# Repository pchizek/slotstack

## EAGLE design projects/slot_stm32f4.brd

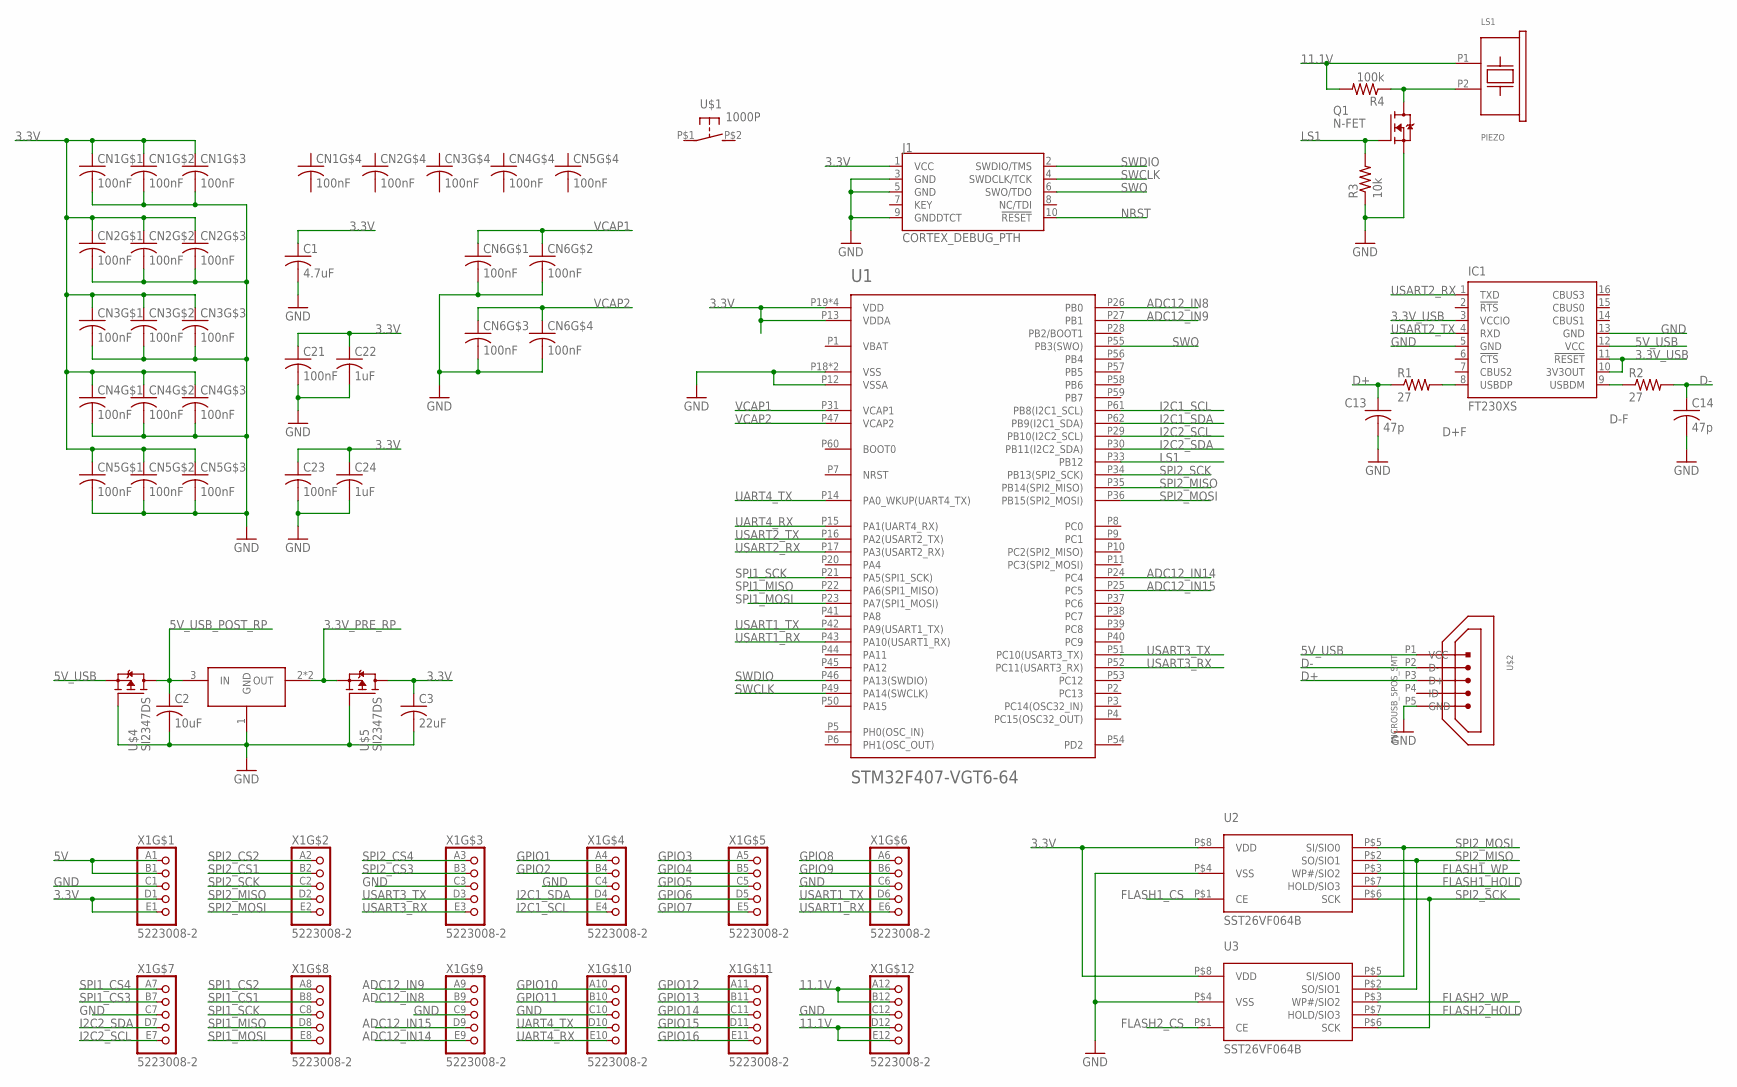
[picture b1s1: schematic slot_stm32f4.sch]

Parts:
C1: 4.7uF; C0805
C2: 10uF; C0805
C3: 22uF; C0805
C13, C14: 47p; C0603
C21, C23: 100nF; C0805
C22, C24: 1uF; C0805
CN1, CN2, CN3, CN4, CN5, CN6: 100nF; CNET_4POS_0612
IC1: FT230XS; SSOP16
J1: CORTEX_DEBUG_PTH; 2X5-PTH-1.27MM
LS1: PIEZO; PKMCS0909E400-R1
Q1: N-FET; NMINI3-R1-B
R1, R2: 27; R0603
R3: 10k; R0603
R4: 100k; R0603
U1: STM32F407-VGT6-64; LQFP64
U2, U3: SST26VF064B; SOIJ
U$1: 1000P; B3U-1000P
U$2: MICROUSB_5POS_SMT; RECPT_SMT_R/A
U$3: AZ1117C; SOT89
U$4, U$5: SI2347DS; SOT23
X1: 5223008-2

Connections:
3.3V: C1.1, C3.1, C21.1, C22.1, C23.1, C24.1, CN1.C1A (1), CN1.C2A (1), CN1.C3A (1), CN2.C1A (1), CN2.C2A (1), CN2.C3A (1), CN3.C1A (1), CN3.C2A (1), CN3.C3A (1), CN4.C1A (1), CN4.C2A (1), CN4.C3A (1), CN5.C1A (1), CN5.C2A (1), CN5.C3A (1), J1.1 (VCC), U1.P13 (VDDA), U1.P19 (VDD), U1.P32 (VDD), U1.P48 (VDD), U1.P64 (VDD), U2.P$8 (VDD), U3.P$8 (VDD), U$5.3 (D), X1.D1 (4), X1.E1 (5)
3.3V_PRE_RP: U$3.2 (OUT), U$3.2@1 (OUT), U$5.2 (S)
3.3V_USB: IC1.3 (VCCIO), IC1.10 (3V3OUT), IC1.11 (!RESET)
5V: X1.A1 (1), X1.B1 (2)
5V_USB: IC1.12 (VCC), U$2.P1 (VCC), U$4.2 (S)
5V_USB_POST_RP: C2.1, U$3.3 (IN), U$4.3 (D)
11.1V: LS1.P1, R4.2, X1.A12 (1), X1.B12 (2), X1.D12 (4), X1.E12 (5)
ADC12_IN8: U1.P26 (PB0), X1.B9 (2)
ADC12_IN9: U1.P27 (PB1), X1.A9 (1)
ADC12_IN14: U1.P24 (PC4), X1.E9 (5)
ADC12_IN15: U1.P25 (PC5), X1.D9 (4)
D+: C13.1, R1.1, U$2.P3 (D+)
D+F: IC1.8 (USBDP), R1.2
D-: C14.1, R2.2, U$2.P2 (D-)
D-F: IC1.9 (USBDM), R2.1
FLASH1_CS: U2.P$1 (CE)
FLASH1_HOLD: U2.P$7 (HOLD/SIO3)
FLASH1_WP: U2.P$3 (WP#/SIO2)
FLASH2_CS: U3.P$1 (CE)
FLASH2_HOLD: U3.P$7 (HOLD/SIO3)
FLASH2_WP: U3.P$3 (WP#/SIO2)
GND: C1.2, C2.2, C3.2, C13.2, C14.2, C21.2, C22.2, C23.2, C24.2, CN1.C1B (2), CN1.C2B (2), CN1.C3B (2), CN2.C1B (2), CN2.C2B (2), CN2.C3B (2), CN3.C1B (2), CN3.C2B (2), CN3.C3B (2), CN4.C1B (2), CN4.C2B (2), CN4.C3B (2), CN5.C1B (2), CN5.C2B (2), CN5.C3B (2), CN6.C1B (2), CN6.C2B (2), CN6.C3B (2), CN6.C4B (2), IC1.5 (GND), IC1.13 (GND), J1.3 (GND), J1.5 (GND), J1.9 (GNDDTCT), Q1.3 (S), R3.1, U1.P12 (VSSA), U1.P18 (VSS), U1.P63 (VSS), U2.P$4 (VSS), U3.P$4 (VSS), U$2.P5 (GND), U$3.1 (GND), U$4.1 (G), U$5.1 (G), X1.C1 (3), X1.C3 (3), X1.C4 (3), X1.C6 (3), X1.C7 (3), X1.C9 (3), X1.C10 (3), X1.C12 (3)
GPIO1: X1.A4 (1)
GPIO2: X1.B4 (2)
GPIO3: X1.A5 (1)
GPIO4: X1.B5 (2)
GPIO5: X1.C5 (3)
GPIO6: X1.D5 (4)
GPIO7: X1.E5 (5)
GPIO8: X1.A6 (1)
GPIO9: X1.B6 (2)
GPIO10: X1.A10 (1)
GPIO11: X1.B10 (2)
GPIO12: X1.A11 (1)
GPIO13: X1.B11 (2)
GPIO14: X1.C11 (3)
GPIO15: X1.D11 (4)
GPIO16: X1.E11 (5)
I2C1_SCL: U1.P61 (PB8(I2C1_SCL)), X1.E4 (5)
I2C1_SDA: U1.P62 (PB9(I2C1_SDA)), X1.D4 (4)
I2C2_SCL: U1.P29 (PB10(I2C2_SCL)), X1.E7 (5)
I2C2_SDA: U1.P30 (PB11(I2C2_SDA)), X1.D7 (4)
LS1: Q1.2 (G), R3.2, U1.P33 (PB12)
unnamed: LS1.P2, Q1.1 (D), R4.1
NRST: J1.10 (!RESET)
SPI1_CS1: X1.B8 (2)
SPI1_CS2: X1.A8 (1)
SPI1_CS3: X1.B7 (2)
SPI1_CS4: X1.A7 (1)
SPI1_MISO: U1.P22 (PA6(SPI1_MISO)), X1.D8 (4)
SPI1_MOSI: U1.P23 (PA7(SPI1_MOSI)), X1.E8 (5)
SPI1_SCK: U1.P21 (PA5(SPI1_SCK)), X1.C8 (3)
SPI2_CS1: X1.B2 (2)
SPI2_CS2: X1.A2 (1)
SPI2_CS3: X1.B3 (2)
SPI2_CS4: X1.A3 (1)
SPI2_MISO: U1.P35 (PB14(SPI2_MISO)), U2.P$2 (SO/SIO1), U3.P$2 (SO/SIO1), X1.D2 (4)
SPI2_MOSI: U1.P36 (PB15(SPI2_MOSI)), U2.P$5 (SI/SIO0), U3.P$5 (SI/SIO0), X1.E2 (5)
SPI2_SCK: U1.P34 (PB13(SPI2_SCK)), U2.P$6 (SCK), U3.P$6 (SCK), X1.C2 (3)
SWCLK: J1.4 (SWDCLK/TCK), U1.P49 (PA14(SWCLK))
SWDIO: J1.2 (SWDIO/TMS), U1.P46 (PA13(SWDIO))
SWO: J1.6 (SWO/TDO), U1.P55 (PB3(SWO))
UART4_RX: U1.P15 (PA1(UART4_RX)), X1.E10 (5)
UART4_TX: U1.P14 (PA0_WKUP(UART4_TX)), X1.D10 (4)
USART1_RX: U1.P43 (PA10(USART1_RX)), X1.E6 (5)
USART1_TX: U1.P42 (PA9(USART1_TX)), X1.D6 (4)
USART2_RX: IC1.1 (TXD), U1.P17 (PA3(USART2_RX))
USART2_TX: IC1.4 (RXD), U1.P16 (PA2(USART2_TX))
USART3_RX: U1.P52 (PC11(USART3_RX)), X1.E3 (5)
USART3_TX: U1.P51 (PC10(USART3_TX)), X1.D3 (4)
VCAP1: CN6.C1A (1), CN6.C2A (1), U1.P31 (VCAP1)
VCAP2: CN6.C3A (1), CN6.C4A (1), U1.P47 (VCAP2)

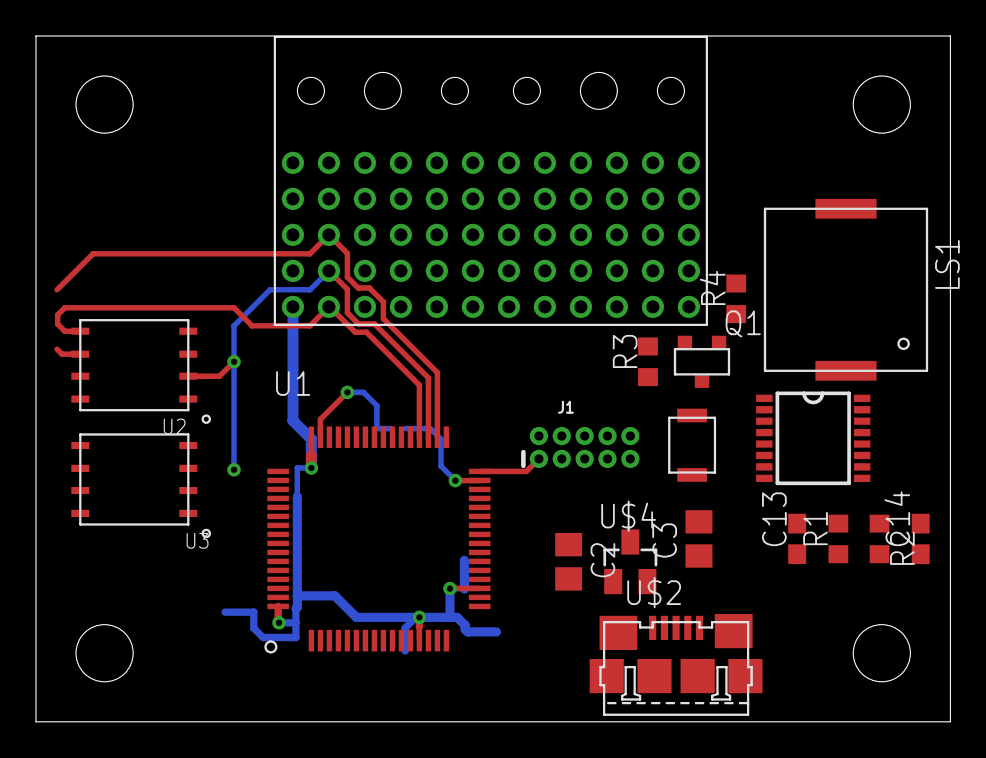
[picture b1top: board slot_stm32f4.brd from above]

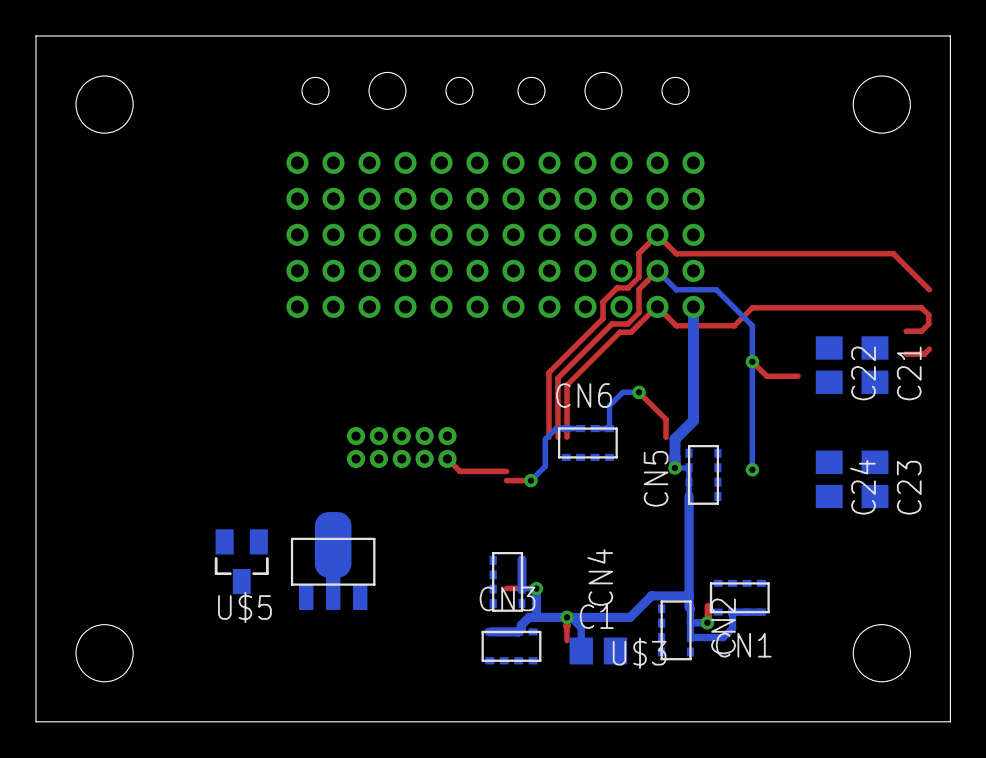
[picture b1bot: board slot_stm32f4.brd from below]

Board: 2 copper layers, 50.8 x 38.1 mm, 32 parts (13 on the bottom side), 41 nets.

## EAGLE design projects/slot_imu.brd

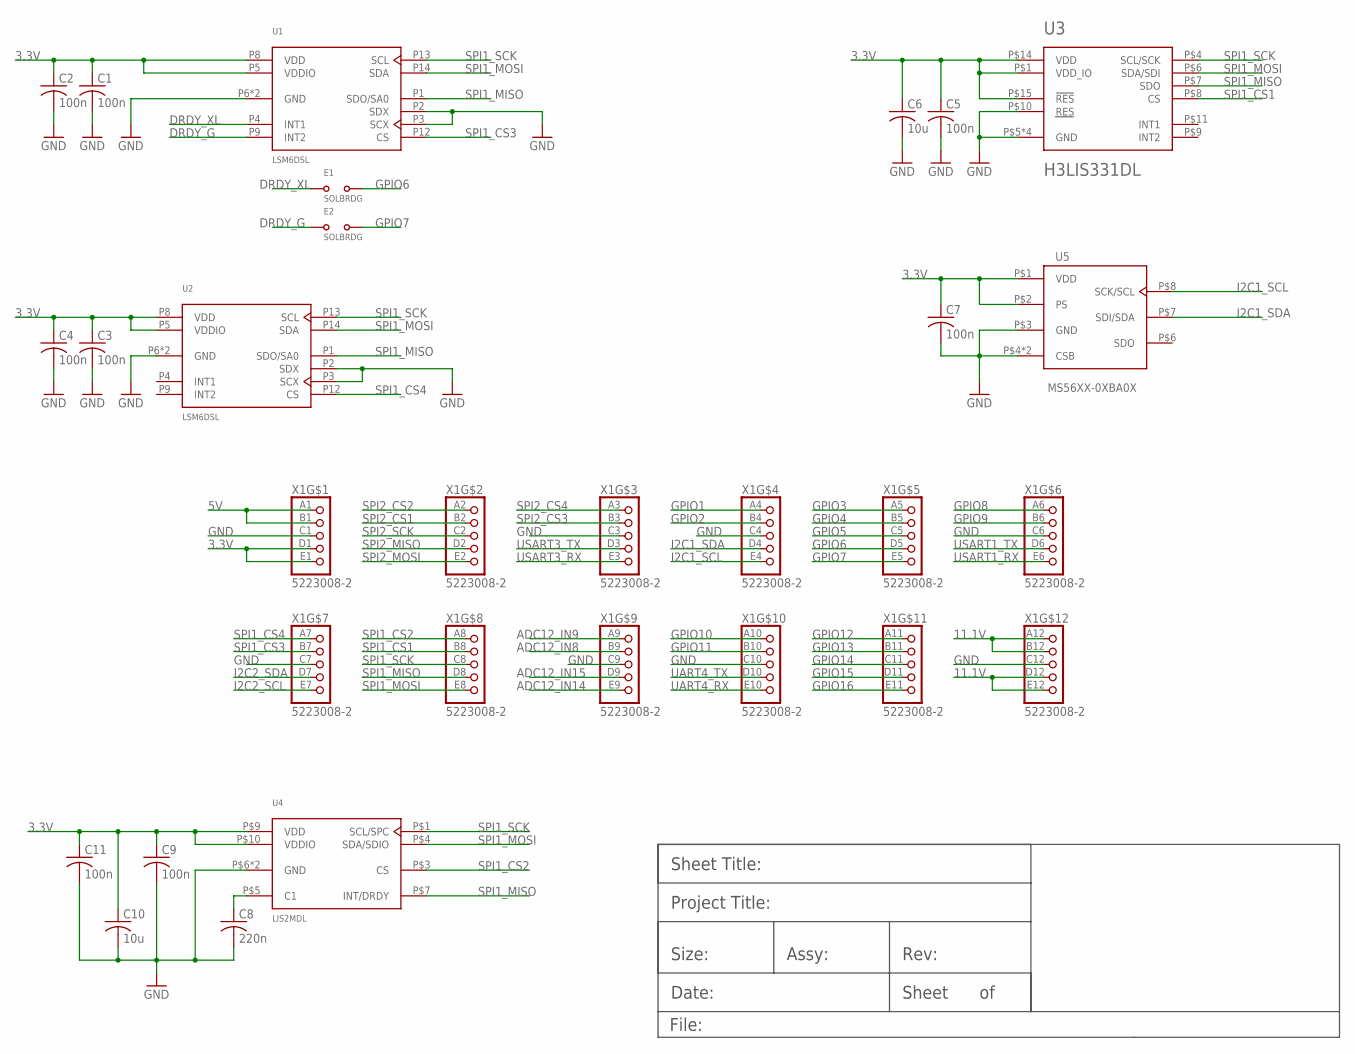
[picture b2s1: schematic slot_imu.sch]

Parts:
C1, C2, C3, C4, C5, C7, C9, C11: 100n; C0805
C6, C10: 10u; C0805
C8: 220n; C0805
E1, E2: SOLBRDG
U1, U2: LSM6DSL; LGA-14
U3: H3LIS331DL; TFLGA-16L
U4: LIS2MDL; LGA-12
U5: MS56XX-0XBA0X; MS56XX
X1: 5223008-2

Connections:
3.3V: C1.1, C2.1, C3.1, C4.1, C5.1, C6.1, C7.1, C9.1, C10.1, C11.1, U1.P5 (VDDIO), U1.P8 (VDD), U2.P5 (VDDIO), U2.P8 (VDD), U3.P$1 (VDD_IO), U3.P$14 (VDD), U3.P$15 (!RES), U4.P$9 (VDD), U4.P$10 (VDDIO), U5.P$1 (VDD), U5.P$2 (PS), X1.D1 (4), X1.E1 (5)
5V: X1.A1 (1), X1.B1 (2)
11.1V: X1.A12 (1), X1.B12 (2), X1.D12 (4), X1.E12 (5)
ADC12_IN8: X1.B9 (2)
ADC12_IN9: X1.A9 (1)
ADC12_IN14: X1.E9 (5)
ADC12_IN15: X1.D9 (4)
DRDY_G: E2.P$1, U1.P9 (INT2)
DRDY_XL: E1.P$1, U1.P4 (INT1)
GND: C1.2, C2.2, C3.2, C4.2, C5.2, C6.2, C7.2, C8.2, C9.2, C10.2, C11.2, U1.P2 (SDX), U1.P3 (SCX), U1.P6 (GND), U1.P7 (GND), U2.P2 (SDX), U2.P3 (SCX), U2.P6 (GND), U2.P7 (GND), U3.P$5 (GND), U3.P$10 (RES), U3.P$12 (GND), U3.P$13 (GND), U3.P$16 (GND), U4.P$6 (GND), U4.P$8 (GND), U5.P$3 (GND), U5.P$4 (CSB), U5.P$5 (CSB), X1.C1 (3), X1.C3 (3), X1.C4 (3), X1.C6 (3), X1.C7 (3), X1.C9 (3), X1.C10 (3), X1.C12 (3)
GPIO1: X1.A4 (1)
GPIO2: X1.B4 (2)
GPIO3: X1.A5 (1)
GPIO4: X1.B5 (2)
GPIO5: X1.C5 (3)
GPIO6: E1.P$2, X1.D5 (4)
GPIO7: E2.P$2, X1.E5 (5)
GPIO8: X1.A6 (1)
GPIO9: X1.B6 (2)
GPIO10: X1.A10 (1)
GPIO11: X1.B10 (2)
GPIO12: X1.A11 (1)
GPIO13: X1.B11 (2)
GPIO14: X1.C11 (3)
GPIO15: X1.D11 (4)
GPIO16: X1.E11 (5)
I2C1_SCL: U5.P$8 (SCK/SCL), X1.E4 (5)
I2C1_SDA: U5.P$7 (SDI/SDA), X1.D4 (4)
I2C2_SCL: X1.E7 (5)
I2C2_SDA: X1.D7 (4)
unnamed: C8.1, U4.P$5 (C1)
SPI1_CS1: U3.P$8 (CS), X1.B8 (2)
SPI1_CS2: U4.P$3 (CS), X1.A8 (1)
SPI1_CS3: U1.P12 (CS), X1.B7 (2)
SPI1_CS4: U2.P12 (CS), X1.A7 (1)
SPI1_MISO: U1.P1 (SDO/SA0), U2.P1 (SDO/SA0), U3.P$7 (SDO), U4.P$7 (INT/DRDY), X1.D8 (4)
SPI1_MOSI: U1.P14 (SDA), U2.P14 (SDA), U3.P$6 (SDA/SDI), U4.P$4 (SDA/SDIO), X1.E8 (5)
SPI1_SCK: U1.P13 (SCL), U2.P13 (SCL), U3.P$4 (SCL/SCK), U4.P$1 (SCL/SPC), X1.C8 (3)
SPI2_CS1: X1.B2 (2)
SPI2_CS2: X1.A2 (1)
SPI2_CS3: X1.B3 (2)
SPI2_CS4: X1.A3 (1)
SPI2_MISO: X1.D2 (4)
SPI2_MOSI: X1.E2 (5)
SPI2_SCK: X1.C2 (3)
UART4_RX: X1.E10 (5)
UART4_TX: X1.D10 (4)
USART1_RX: X1.E6 (5)
USART1_TX: X1.D6 (4)
USART3_RX: X1.E3 (5)
USART3_TX: X1.D3 (4)

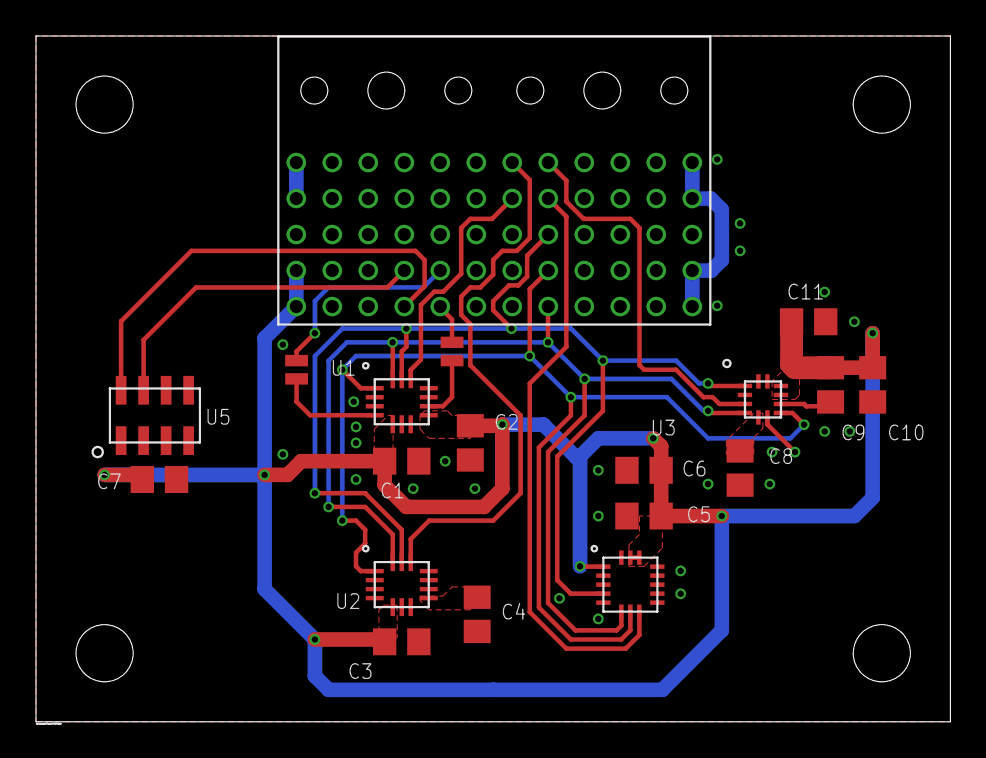
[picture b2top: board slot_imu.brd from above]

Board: 2 copper layers, 50.8 x 38.1 mm, 19 parts (0 on the bottom side), 18 nets.

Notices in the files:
parts and their libraries:
SparkFun-Connectors: Licensing: Creative Commons ShareAlike 4.0 International - https://creativecommons.org/licenses/by-sa/4.0
